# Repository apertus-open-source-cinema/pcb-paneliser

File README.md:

# pcb-paneliser
Creating panels from individual PCBs in an as automated way as possible.

## Setup
These scripts were built for python3.

  * Execute ```pip3 install -r requirements.txt``` to install required modules
  * Run ```python3 stage1_generate_mixed_beta_panel.py``` to generate mixed PCB panel
  * Run ```python3 stage2_generate_multi_mixed_beta_panel.py``` to generate a big panel consisting of multiple mixed PCB panels
  * Run ```python3 stage3_generate_stage1_stencils.py``` to generate stencils for mixed PCB panel

## Extracting impedance relevant layers

  * Update the filenames to extract in ```extract_impedance_stage1.py``` and then execute ```python3 extract_impedance_stage1.py``` - this extracts all traces with a specific netclass from the *.brd files and creates a new output file called <boardname>_impedance.brd inside output_impedance_filtered/
  * Extract gerber layers throught Eagles oshpark-4layer.cam into output_impedance_filtered/gerber_export and use rotate_90_ccw.sh on them if required.
  * Update output_impedance_filtered/stage1_generate_mixed_beta_impedance_panel.py again withe the correct board names and run ```python3 stage1_generate_mixed_beta_impedance_panel.py```

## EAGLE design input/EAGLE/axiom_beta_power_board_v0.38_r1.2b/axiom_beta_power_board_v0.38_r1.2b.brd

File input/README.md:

# Export from EAGLE to Gerber

This guide should cover the process to go from eagle _*.brd_ file to the catalog of Gerber input files for stage 1.

## Steps:
* Open _*.brd_ and _*.sch_ files in Eagle
* Choose assembly variant in dropdown menu then resave both _*.brd_ and _*.sch_ files
  * Select base (**empty** variant) for panels and **Tele** for stencil and BOM
* in Eagle go to **File -> CAM Processor**, then in the newly opened window **File -> Open -> Job**
* Choose the **oshpark-4layer.cam** file from this directory
* Click **Process Job** - the files will be written to the same directory where the _*.brd_ file resides
  * Confirm the warning about large data with **Yes to all**

# using the rotate script
copy the **rotate_90_ccw.sh** script into a subfolder containing gerber files like the **base_variant** folder.
Run **rotate_90_ccw.sh** with the name of the board and subfolder as argument.
It will rename the source to ..._original, but you should grab the data from the new folder and paste it over the original one, delete new folder and remove _original. Bit cumbersome currently but works for now.

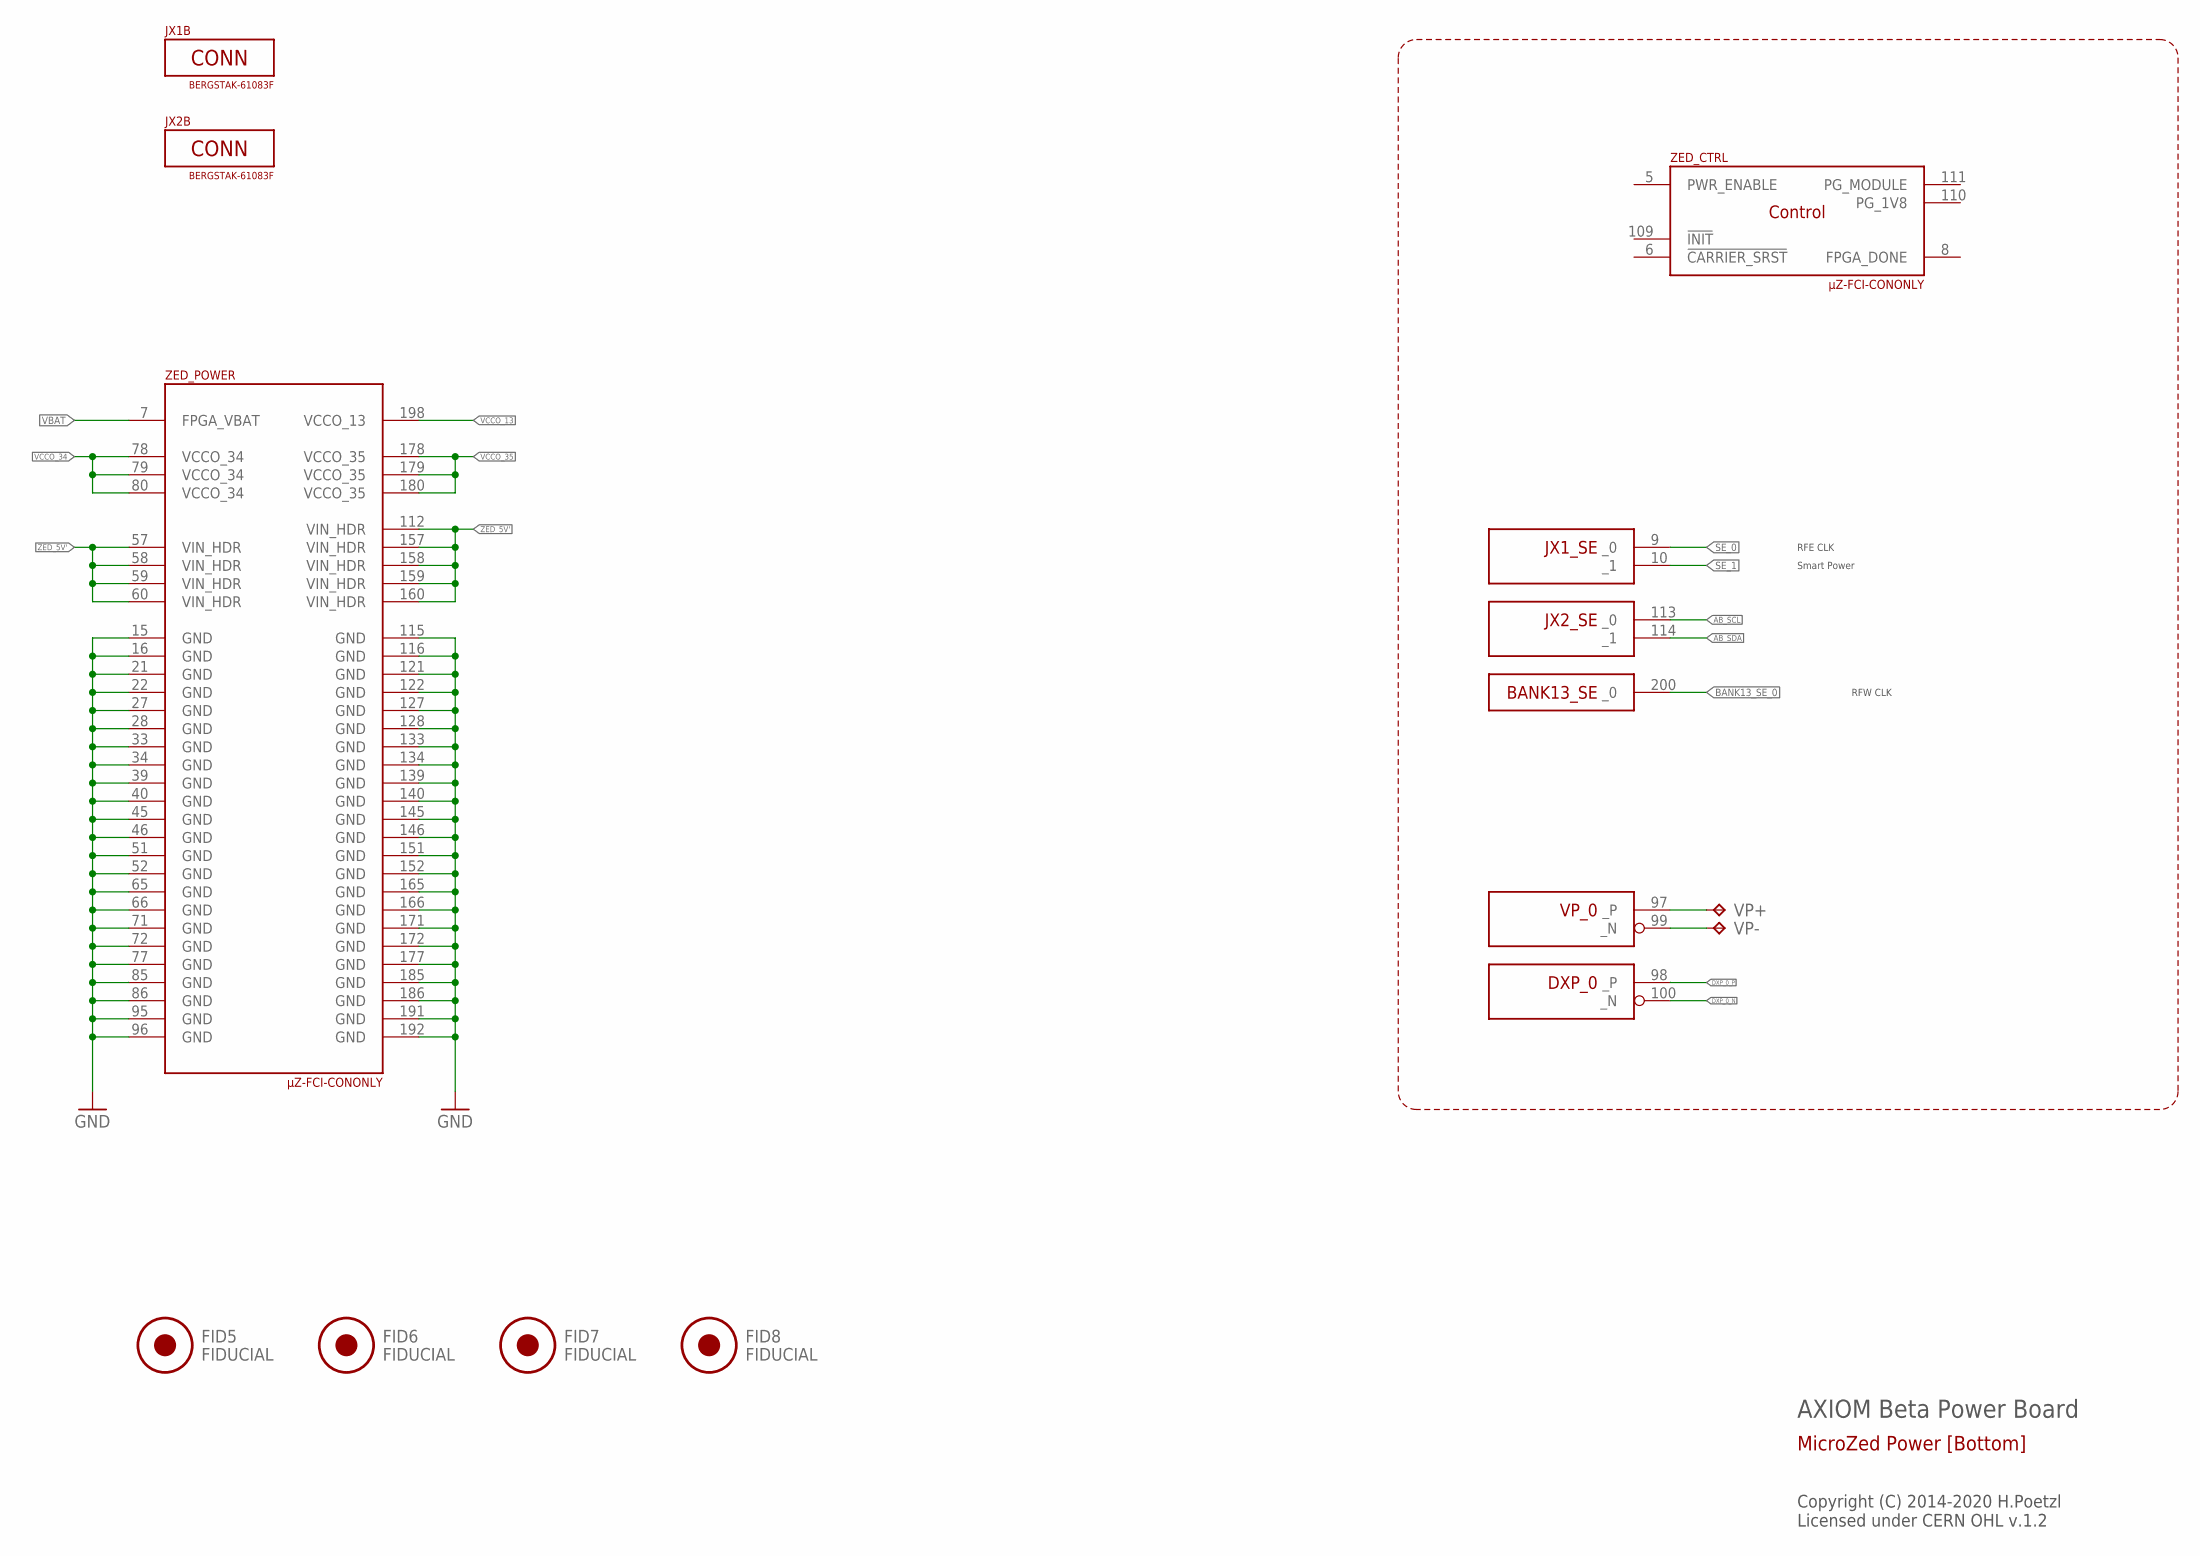
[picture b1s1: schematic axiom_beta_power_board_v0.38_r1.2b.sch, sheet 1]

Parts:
FID5, FID6, FID7, FID8: FIDUCIAL; FID_ARROW
JX1B, JX2B: BERGSTAK-61083F; 61083-FAKE
VP+: TPTP16SQ; TP16SQ
VP-: TPTP16SQ; TP16SQ
ZED: µZ-FCI-CONONLY; µZ-CONONLY

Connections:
AB_SCL: ZED.113 (_0); also elsewhere on the board
AB_SDA: ZED.114 (_1); also elsewhere on the board
BANK13_SE_0: ZED.200 (_0); also elsewhere on the board
DXP_0_N: ZED.100 (_N)
DXP_0_P: ZED.98 (_P)
GND: ZED.15 (GND), ZED.16 (GND), ZED.21 (GND), ZED.22 (GND), ZED.27 (GND), ZED.28 (GND), ZED.33 (GND), ZED.34 (GND), ZED.39 (GND), ZED.40 (GND), ZED.45 (GND), ZED.46 (GND), ZED.51 (GND), ZED.52 (GND), ZED.65 (GND), ZED.66 (GND), ZED.71 (GND), ZED.72 (GND), ZED.77 (GND), ZED.85 (GND), ZED.86 (GND), ZED.95 (GND), ZED.96 (GND), ZED.115 (GND), ZED.116 (GND), ZED.121 (GND), ZED.122 (GND), ZED.127 (GND), ZED.128 (GND), ZED.133 (GND), ZED.134 (GND), ZED.139 (GND), ZED.140 (GND), ZED.145 (GND), ZED.146 (GND), ZED.151 (GND), ZED.152 (GND), ZED.165 (GND), ZED.166 (GND), ZED.171 (GND), ZED.172 (GND), ZED.177 (GND), ZED.185 (GND), ZED.186 (GND), ZED.191 (GND), ZED.192 (GND); also elsewhere on the board
SE_0: ZED.9 (_0); also elsewhere on the board
SE_1: ZED.10 (_1); also elsewhere on the board
VBAT: ZED.7 (FPGA_VBAT)
VCCO_13: ZED.198 (VCCO_13); also elsewhere on the board
VCCO_34: ZED.78 (VCCO_34), ZED.79 (VCCO_34), ZED.80 (VCCO_34); also elsewhere on the board
VCCO_35: ZED.178 (VCCO_35), ZED.179 (VCCO_35), ZED.180 (VCCO_35); also elsewhere on the board
VP_0_N: VP-.TP, ZED.99 (_N)
VP_0_P: VP+.TP, ZED.97 (_P)
ZED_5V': ZED.57 (VIN_HDR), ZED.58 (VIN_HDR), ZED.59 (VIN_HDR), ZED.60 (VIN_HDR), ZED.112 (VIN_HDR), ZED.157 (VIN_HDR), ZED.158 (VIN_HDR), ZED.159 (VIN_HDR), ZED.160 (VIN_HDR); also elsewhere on the board

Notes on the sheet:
AXIOM Beta Power Board
Copyright (C) 2014-2020 H.Poetzl Licensed under CERN OHL v.1.2
MicroZed Power [Bottom]
Smart Power
RFE CLK
RFW CLK

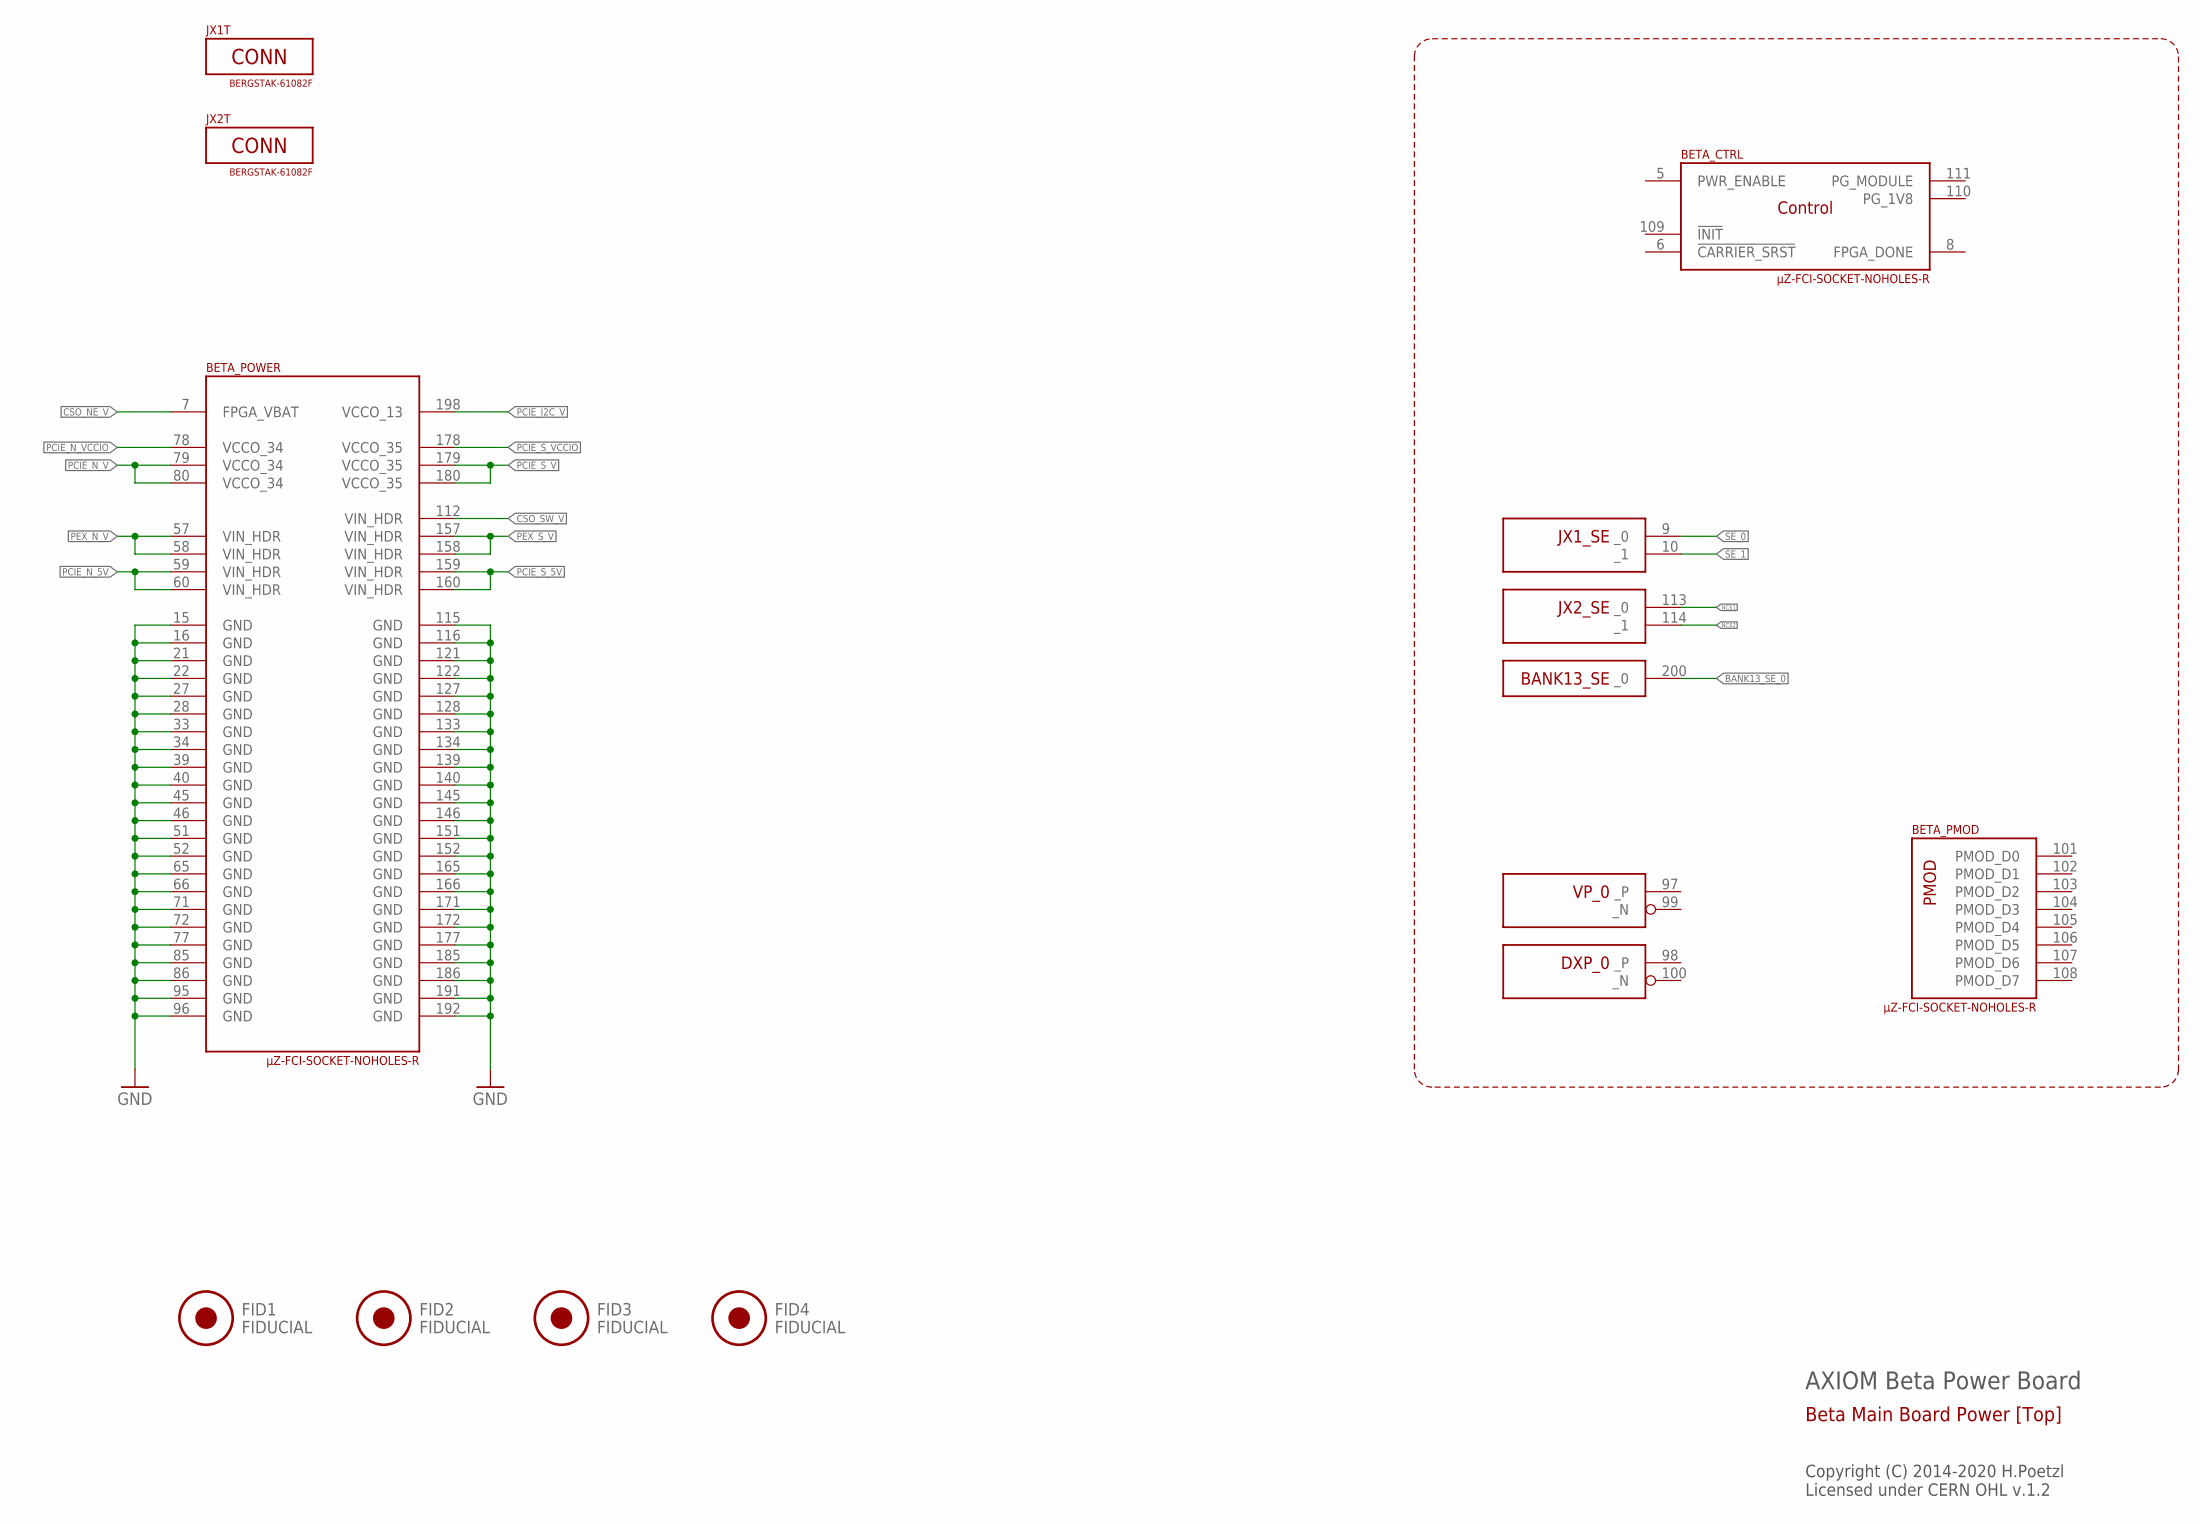
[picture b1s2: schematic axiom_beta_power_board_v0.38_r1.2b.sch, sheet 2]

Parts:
BETA: µZ-FCI-SOCKET-NOHOLES-R; µZ-SOCKET-NOHOLES-R
FID1, FID2, FID3, FID4: FIDUCIAL; FID_ARROW
JX1T, JX2T: BERGSTAK-61082F; 61082-FAKE

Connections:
BANK13_SE_0: BETA.200 (_0); also elsewhere on the board
CSO_NE_V: BETA.7 (FPGA_VBAT); also elsewhere on the board
CSO_SW_V: BETA.112 (VIN_HDR); also elsewhere on the board
GND: BETA.15 (GND), BETA.16 (GND), BETA.21 (GND), BETA.22 (GND), BETA.27 (GND), BETA.28 (GND), BETA.33 (GND), BETA.34 (GND), BETA.39 (GND), BETA.40 (GND), BETA.45 (GND), BETA.46 (GND), BETA.51 (GND), BETA.52 (GND), BETA.65 (GND), BETA.66 (GND), BETA.71 (GND), BETA.72 (GND), BETA.77 (GND), BETA.85 (GND), BETA.86 (GND), BETA.95 (GND), BETA.96 (GND), BETA.115 (GND), BETA.116 (GND), BETA.121 (GND), BETA.122 (GND), BETA.127 (GND), BETA.128 (GND), BETA.133 (GND), BETA.134 (GND), BETA.139 (GND), BETA.140 (GND), BETA.145 (GND), BETA.146 (GND), BETA.151 (GND), BETA.152 (GND), BETA.165 (GND), BETA.166 (GND), BETA.171 (GND), BETA.172 (GND), BETA.177 (GND), BETA.185 (GND), BETA.186 (GND), BETA.191 (GND), BETA.192 (GND); also elsewhere on the board
NC$1: BETA.113 (_0)
NC$2: BETA.114 (_1)
PCIE_I2C_V: BETA.198 (VCCO_13)
PCIE_N_5V: BETA.59 (VIN_HDR), BETA.60 (VIN_HDR)
PCIE_N_V: BETA.79 (VCCO_34), BETA.80 (VCCO_34); also elsewhere on the board
PCIE_N_VCCIO: BETA.78 (VCCO_34)
PCIE_S_5V: BETA.159 (VIN_HDR), BETA.160 (VIN_HDR)
PCIE_S_V: BETA.179 (VCCO_35), BETA.180 (VCCO_35); also elsewhere on the board
PCIE_S_VCCIO: BETA.178 (VCCO_35)
PEX_N_V: BETA.57 (VIN_HDR), BETA.58 (VIN_HDR)
PEX_S_V: BETA.157 (VIN_HDR), BETA.158 (VIN_HDR)
SE_0: BETA.9 (_0); also elsewhere on the board
SE_1: BETA.10 (_1); also elsewhere on the board

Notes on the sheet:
AXIOM Beta Power Board
Copyright (C) 2014-2020 H.Poetzl Licensed under CERN OHL v.1.2
Beta Main Board Power [Top]

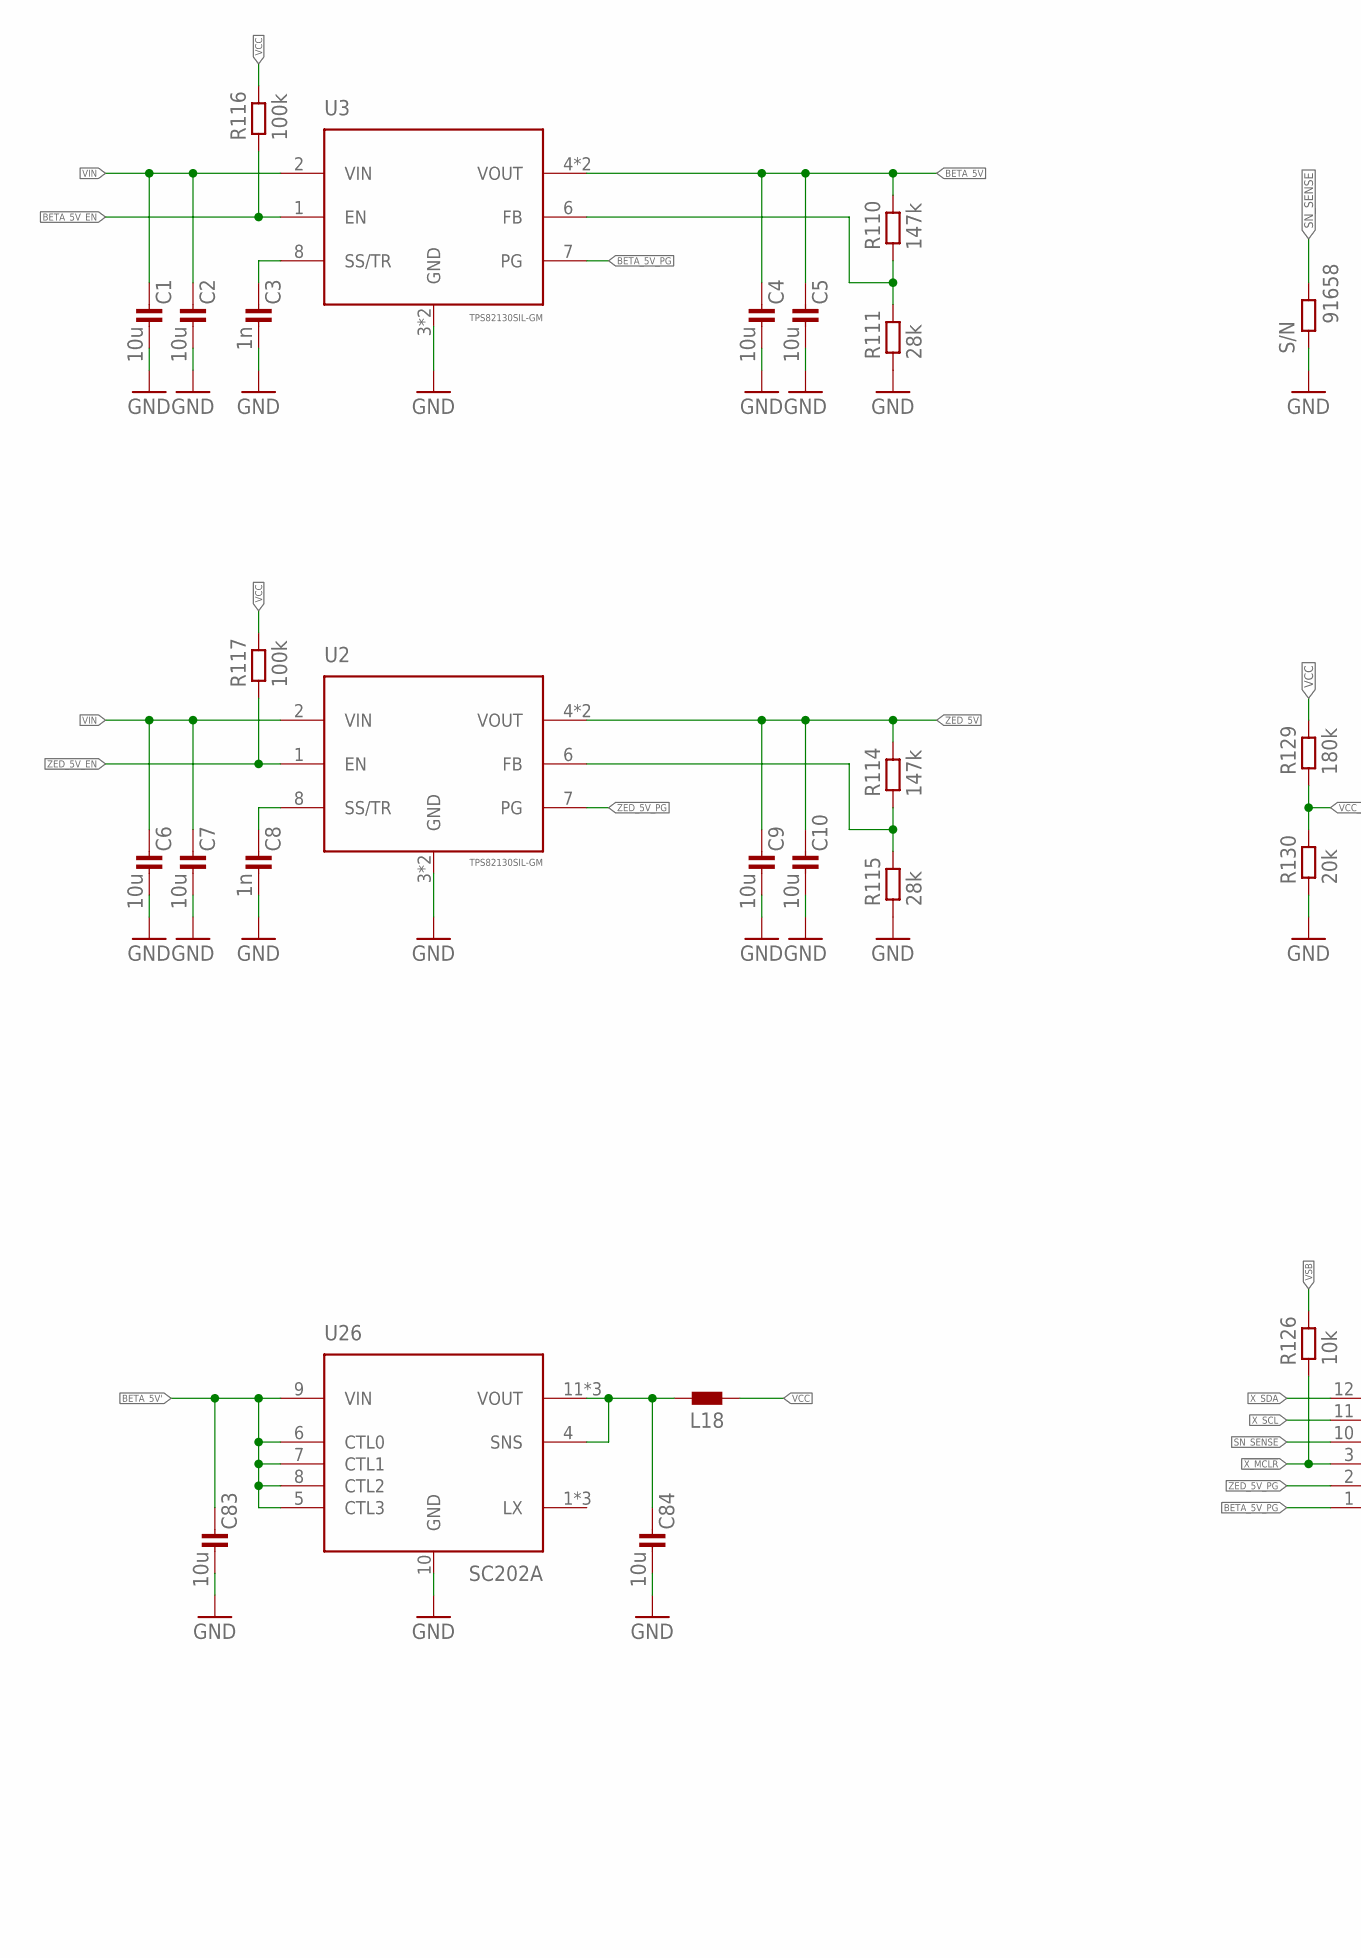
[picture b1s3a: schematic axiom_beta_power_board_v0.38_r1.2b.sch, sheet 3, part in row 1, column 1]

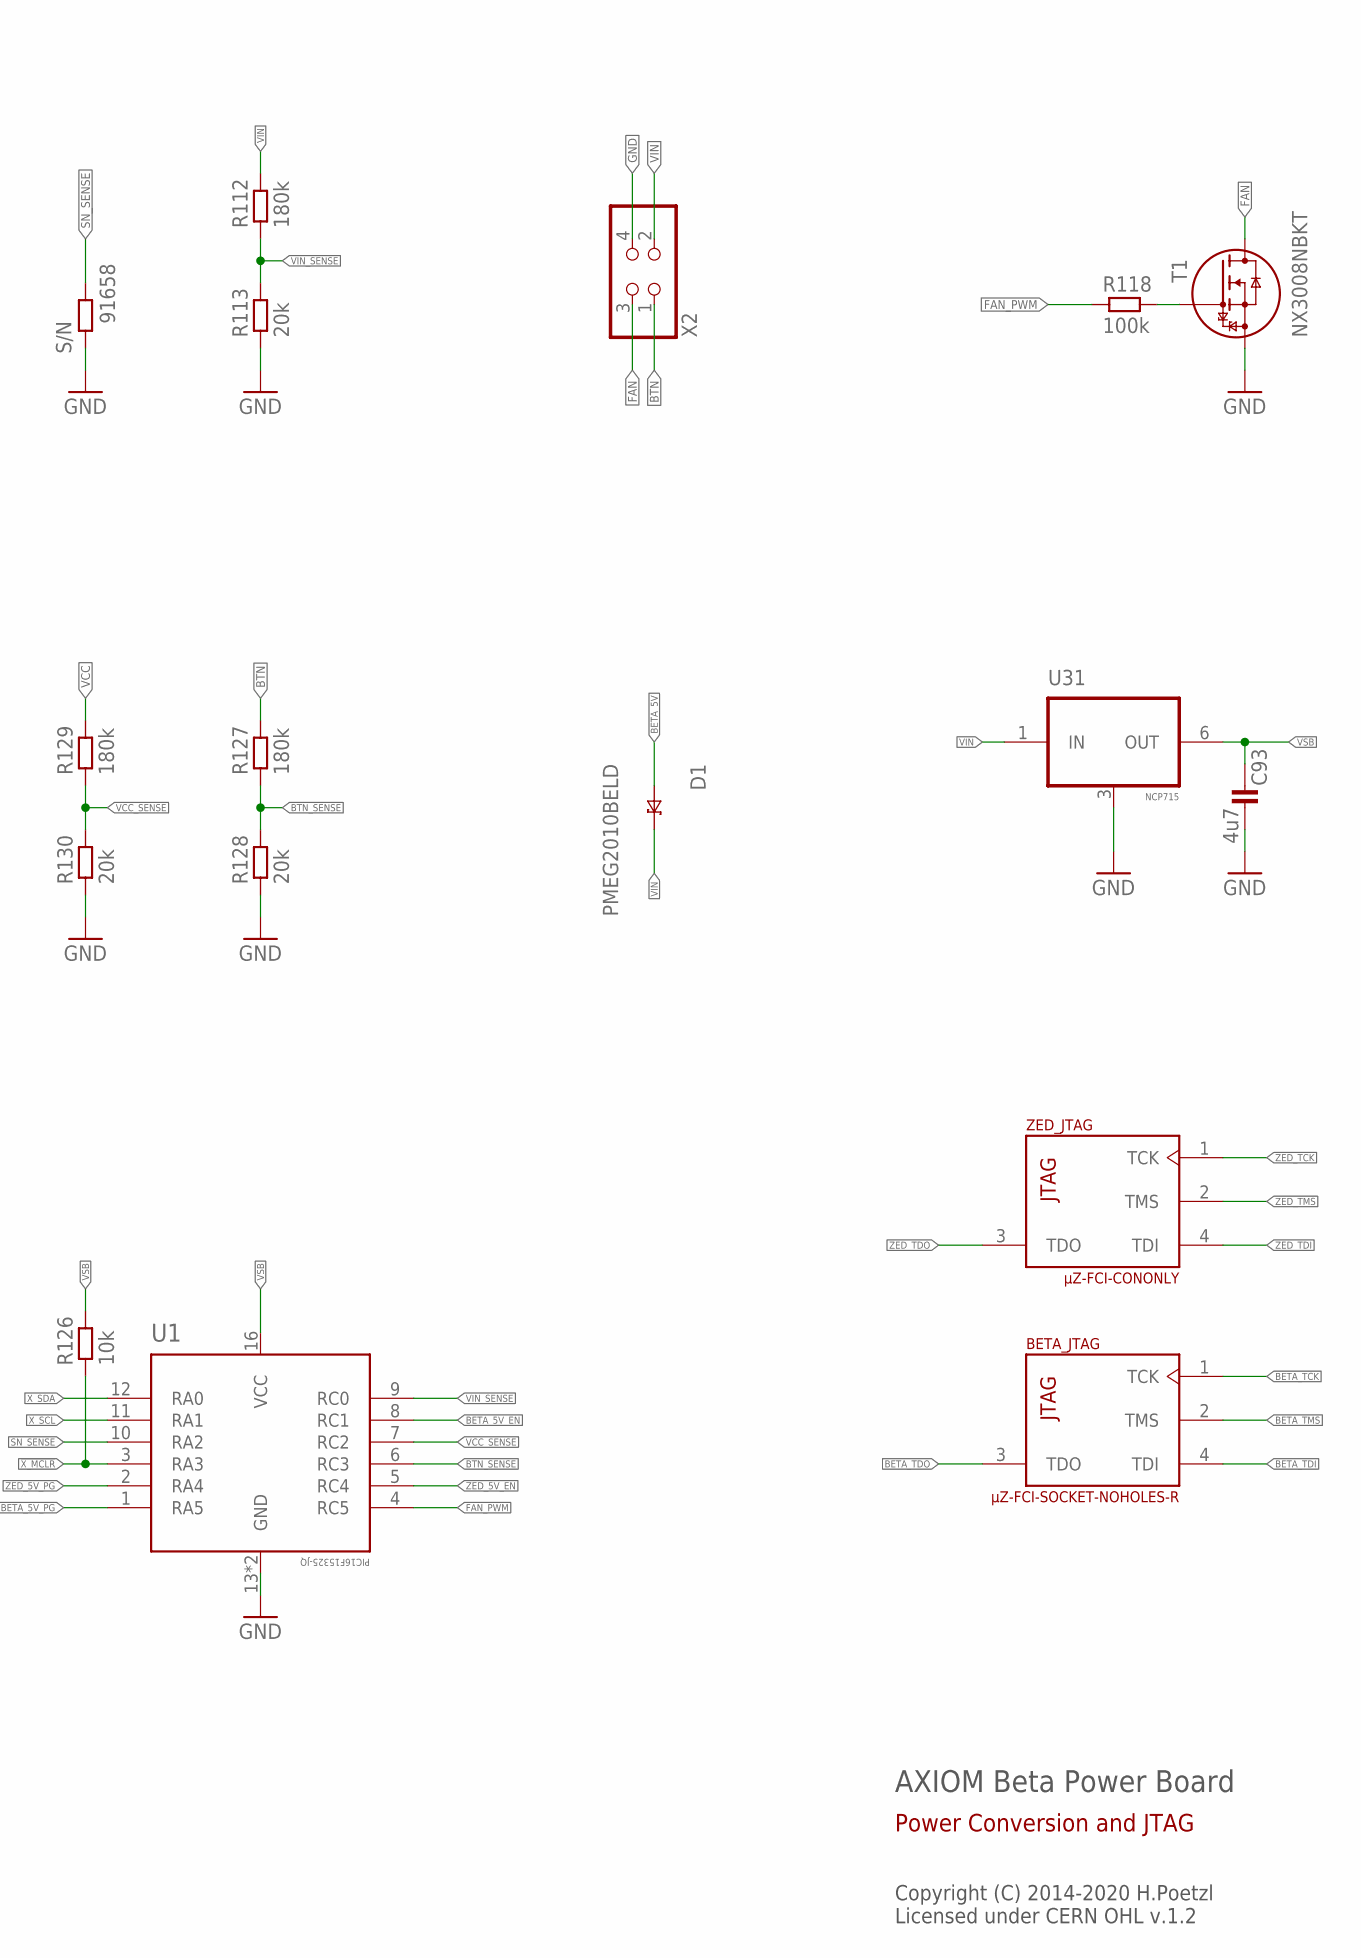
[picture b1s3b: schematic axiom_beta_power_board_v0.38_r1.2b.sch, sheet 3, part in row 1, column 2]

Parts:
BETA: µZ-FCI-SOCKET-NOHOLES-R; µZ-SOCKET-NOHOLES-R
C1, C5, C6, C10: 10u; 0603-B
C2, C4, C7, C9: 10u; 1206-C
C3, C8: 1n; 0402-C
C83, C84: 10u; 0603-C
C93: 4u7; 0402-B
D1: PMEG2010BELD; DFN1006D-2
L18: L0603-C; 0603-C
R110, R114: 147k; 0402-C
R111, R115: 28k; 0402-C
R112: 180k; 0402-B
R113: 20k; 0402-B
R116, R117: 100k; 0402-B
R118: 100k; 0402-C
R126: 10k; 0402-B
R127, R129: 180k; 0402-C
R128, R130: 20k; 0402-C
S/N: 91658; 3X2MM
T1: NX3008NBKT; SOT416
U1: PIC16F15325-JQ; UQFN65P400X400X100-17N
U2, U3: TPS82130SIL-GM; SIL0008D-GM
U26: SC202A; MLPQ-13
U31: NCP715; DFN150X150X50-6N
X2: PINHD-2X02_2.54-90°; 2X02/90
ZED: µZ-FCI-CONONLY; µZ-CONONLY

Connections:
!X_MCLR: R126.2, U1.3 (RA3); also elsewhere on the board
BETA_5V: C4.1, C5.1, D1.A, R110.1, U3.4 (VOUT), U3.5 (VOUT); also elsewhere on the board
BETA_5V': C83.1, U26.5 (CTL3), U26.6 (CTL0), U26.7 (CTL1), U26.8 (CTL2), U26.9 (VIN); also elsewhere on the board
BETA_5V_EN: R116.2, U1.8 (RC1), U3.1 (EN)
BETA_5V_PG: U1.1 (RA5), U3.7 (PG)
BETA_TCK: BETA.1 (TCK)
BETA_TDI: BETA.4 (TDI)
BETA_TDO: BETA.3 (TDO)
BETA_TMS: BETA.2 (TMS)
BTN: R127.1, X2.1
BTN_SENSE: R127.2, R128.1, U1.6 (RC3)
FAN: T1.3 (D), X2.3
FAN_PWM: R118.2, U1.4 (RC5)
GND: C1.2, C2.2, C3.2, C4.2, C5.2, C6.2, C7.2, C8.2, C9.2, C10.2, C83.2, C84.2, C93.2, R111.2, R113.2, R115.2, R128.2, R130.2, S/N.1, T1.2 (S), U1.13 (GND), U1.EP (GND), U2.3 (GND), U2.EPAD (GND), U3.3 (GND), U3.EPAD (GND), U26.10 (GND), U31.3 (GND), X2.4; also elsewhere on the board
unnamed: C8.1, U2.8 (SS/TR)
unnamed: C3.1, U3.8 (SS/TR)
unnamed: R118.1, T1.1 (G)
unnamed: R110.2, R111.1, U3.6 (FB)
unnamed: R114.2, R115.1, U2.6 (FB)
REGOUT: C84.1, L18.1, U26.4 (SNS), U26.11 (VOUT), U26.12 (VOUT), U26.13 (VOUT)
SN_SENSE: S/N.2, U1.10 (RA2)
VCC: L18.2, R116.1, R117.1, R129.1; also elsewhere on the board
VCC_SENSE: R129.2, R130.1, U1.7 (RC2)
VIN: C1.1, C2.1, C6.1, C7.1, D1.C (K), R112.1, U2.2 (VIN), U3.2 (VIN), U31.1 (IN), X2.2
VIN_SENSE: R112.2, R113.1, U1.9 (RC0)
VSB: C93.1, R126.1, U1.16 (VCC), U31.6 (OUT); also elsewhere on the board
X_SCL: U1.11 (RA1); also elsewhere on the board
X_SDA: U1.12 (RA0); also elsewhere on the board
ZED_5V: C9.1, C10.1, R114.1, U2.4 (VOUT), U2.5 (VOUT); also elsewhere on the board
ZED_5V_EN: R117.2, U1.5 (RC4), U2.1 (EN)
ZED_5V_PG: U1.2 (RA4), U2.7 (PG)
ZED_TCK: ZED.1 (TCK)
ZED_TDI: ZED.4 (TDI)
ZED_TDO: ZED.3 (TDO)
ZED_TMS: ZED.2 (TMS)

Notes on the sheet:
AXIOM Beta Power Board
Copyright (C) 2014-2020 H.Poetzl Licensed under CERN OHL v.1.2
Power Conversion and JTAG

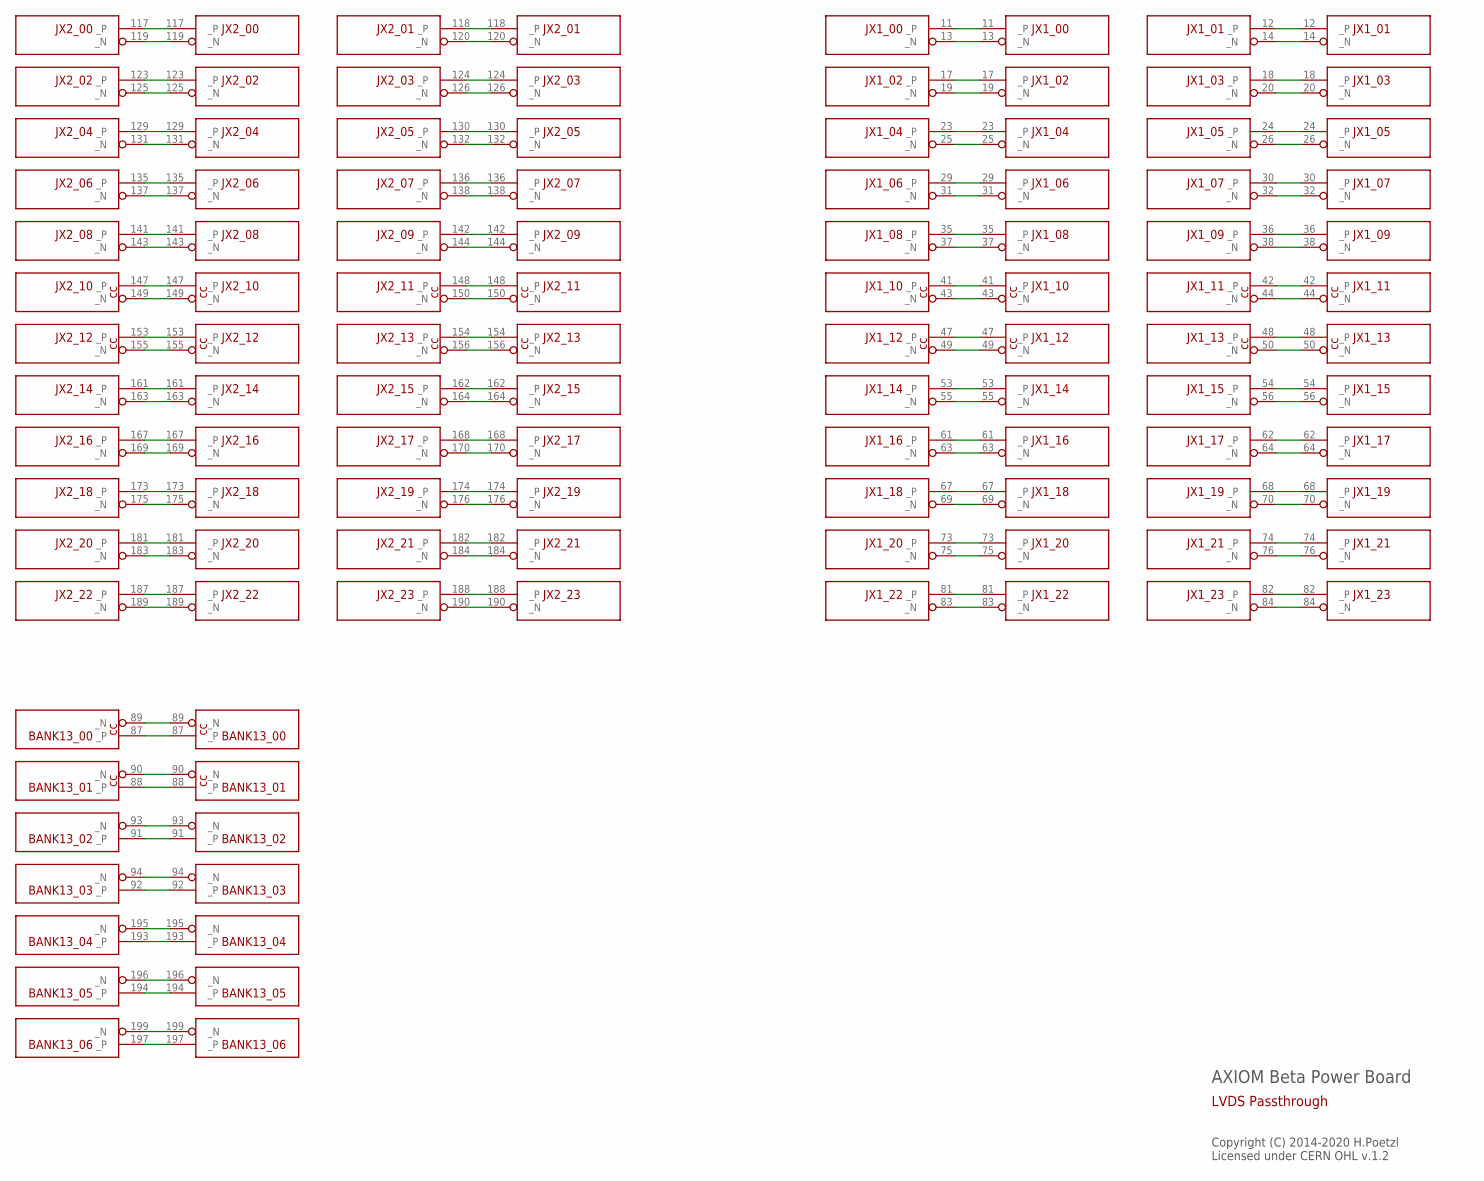
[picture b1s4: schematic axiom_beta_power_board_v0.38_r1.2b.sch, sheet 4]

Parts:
BETA: µZ-FCI-SOCKET-NOHOLES-R; µZ-SOCKET-NOHOLES-R
ZED: µZ-FCI-CONONLY; µZ-CONONLY

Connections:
BANK13_00_N: BETA.89 (_N), ZED.89 (_N)
BANK13_00_P: BETA.87 (_P), ZED.87 (_P)
BANK13_01_N: BETA.90 (_N), ZED.90 (_N)
BANK13_01_P: BETA.88 (_P), ZED.88 (_P)
BANK13_02_N: BETA.93 (_N), ZED.93 (_N)
BANK13_02_P: BETA.91 (_P), ZED.91 (_P)
BANK13_03_N: BETA.94 (_N), ZED.94 (_N)
BANK13_03_P: BETA.92 (_P), ZED.92 (_P)
BANK13_04_N: BETA.195 (_N), ZED.195 (_N)
BANK13_04_P: BETA.193 (_P), ZED.193 (_P)
BANK13_05_N: BETA.196 (_N), ZED.196 (_N)
BANK13_05_P: BETA.194 (_P), ZED.194 (_P)
BANK13_06_N: BETA.199 (_N), ZED.199 (_N)
BANK13_06_P: BETA.197 (_P), ZED.197 (_P)
JX1_00_N: BETA.13 (_N), ZED.13 (_N)
JX1_00_P: BETA.11 (_P), ZED.11 (_P)
JX1_01_N: BETA.14 (_N), ZED.14 (_N)
JX1_01_P: BETA.12 (_P), ZED.12 (_P)
JX1_02_N: BETA.19 (_N), ZED.19 (_N)
JX1_02_P: BETA.17 (_P), ZED.17 (_P)
JX1_03_N: BETA.20 (_N), ZED.20 (_N)
JX1_03_P: BETA.18 (_P), ZED.18 (_P)
JX1_04_N: BETA.25 (_N), ZED.25 (_N)
JX1_04_P: BETA.23 (_P), ZED.23 (_P)
JX1_05_N: BETA.26 (_N), ZED.26 (_N)
JX1_05_P: BETA.24 (_P), ZED.24 (_P)
JX1_06_N: BETA.31 (_N), ZED.31 (_N)
JX1_06_P: BETA.29 (_P), ZED.29 (_P)
JX1_07_N: BETA.32 (_N), ZED.32 (_N)
JX1_07_P: BETA.30 (_P), ZED.30 (_P)
JX1_08_N: BETA.37 (_N), ZED.37 (_N)
JX1_08_P: BETA.35 (_P), ZED.35 (_P)
JX1_09_N: BETA.38 (_N), ZED.38 (_N)
JX1_09_P: BETA.36 (_P), ZED.36 (_P)
JX1_10_N: BETA.43 (_N), ZED.43 (_N)
JX1_10_P: BETA.41 (_P), ZED.41 (_P)
JX1_11_N: BETA.44 (_N), ZED.44 (_N)
JX1_11_P: BETA.42 (_P), ZED.42 (_P)
JX1_12_N: BETA.49 (_N), ZED.49 (_N)
JX1_12_P: BETA.47 (_P), ZED.47 (_P)
JX1_13_N: BETA.50 (_N), ZED.50 (_N)
JX1_13_P: BETA.48 (_P), ZED.48 (_P)
JX1_14_N: BETA.55 (_N), ZED.55 (_N)
JX1_14_P: BETA.53 (_P), ZED.53 (_P)
JX1_15_N: BETA.56 (_N), ZED.56 (_N)
JX1_15_P: BETA.54 (_P), ZED.54 (_P)
JX1_16_N: BETA.63 (_N), ZED.63 (_N)
JX1_16_P: BETA.61 (_P), ZED.61 (_P)
JX1_17_N: BETA.64 (_N), ZED.64 (_N)
JX1_17_P: BETA.62 (_P), ZED.62 (_P)
JX1_18_N: BETA.69 (_N), ZED.69 (_N)
JX1_18_P: BETA.67 (_P), ZED.67 (_P)
JX1_19_N: BETA.70 (_N), ZED.70 (_N)
JX1_19_P: BETA.68 (_P), ZED.68 (_P)
JX1_20_N: BETA.75 (_N), ZED.75 (_N)
JX1_20_P: BETA.73 (_P), ZED.73 (_P)
JX1_21_N: BETA.76 (_N), ZED.76 (_N)
JX1_21_P: BETA.74 (_P), ZED.74 (_P)
JX1_22_N: BETA.83 (_N), ZED.83 (_N)
JX1_22_P: BETA.81 (_P), ZED.81 (_P)
JX1_23_N: BETA.84 (_N), ZED.84 (_N)
JX1_23_P: BETA.82 (_P), ZED.82 (_P)
JX2_00_N: BETA.119 (_N), ZED.119 (_N)
JX2_00_P: BETA.117 (_P), ZED.117 (_P)
JX2_01_N: BETA.120 (_N), ZED.120 (_N)
JX2_01_P: BETA.118 (_P), ZED.118 (_P)
JX2_02_N: BETA.125 (_N), ZED.125 (_N)
JX2_02_P: BETA.123 (_P), ZED.123 (_P)
JX2_03_N: BETA.126 (_N), ZED.126 (_N)
JX2_03_P: BETA.124 (_P), ZED.124 (_P)
JX2_04_N: BETA.131 (_N), ZED.131 (_N)
JX2_04_P: BETA.129 (_P), ZED.129 (_P)
JX2_05_N: BETA.132 (_N), ZED.132 (_N)
JX2_05_P: BETA.130 (_P), ZED.130 (_P)
JX2_06_N: BETA.137 (_N), ZED.137 (_N)
JX2_06_P: BETA.135 (_P), ZED.135 (_P)
JX2_07_N: BETA.138 (_N), ZED.138 (_N)
JX2_07_P: BETA.136 (_P), ZED.136 (_P)
JX2_08_N: BETA.143 (_N), ZED.143 (_N)
JX2_08_P: BETA.141 (_P), ZED.141 (_P)
JX2_09_N: BETA.144 (_N), ZED.144 (_N)
JX2_09_P: BETA.142 (_P), ZED.142 (_P)
JX2_10_N: BETA.149 (_N), ZED.149 (_N)
JX2_10_P: BETA.147 (_P), ZED.147 (_P)
JX2_11_N: BETA.150 (_N), ZED.150 (_N)
JX2_11_P: BETA.148 (_P), ZED.148 (_P)
JX2_12_N: BETA.155 (_N), ZED.155 (_N)
JX2_12_P: BETA.153 (_P), ZED.153 (_P)
JX2_13_N: BETA.156 (_N), ZED.156 (_N)
JX2_13_P: BETA.154 (_P), ZED.154 (_P)
JX2_14_N: BETA.163 (_N), ZED.163 (_N)
JX2_14_P: BETA.161 (_P), ZED.161 (_P)
JX2_15_N: BETA.164 (_N), ZED.164 (_N)
JX2_15_P: BETA.162 (_P), ZED.162 (_P)
JX2_16_N: BETA.169 (_N), ZED.169 (_N)
JX2_16_P: BETA.167 (_P), ZED.167 (_P)
JX2_17_N: BETA.170 (_N), ZED.170 (_N)
JX2_17_P: BETA.168 (_P), ZED.168 (_P)
JX2_18_N: BETA.175 (_N), ZED.175 (_N)
JX2_18_P: BETA.173 (_P), ZED.173 (_P)
JX2_19_N: BETA.176 (_N), ZED.176 (_N)
JX2_19_P: BETA.174 (_P), ZED.174 (_P)
JX2_20_N: BETA.183 (_N), ZED.183 (_N)
JX2_20_P: BETA.181 (_P), ZED.181 (_P)
JX2_21_N: BETA.184 (_N), ZED.184 (_N)
JX2_21_P: BETA.182 (_P), ZED.182 (_P)
JX2_22_N: BETA.189 (_N), ZED.189 (_N)
JX2_22_P: BETA.187 (_P), ZED.187 (_P)
JX2_23_N: BETA.190 (_N), ZED.190 (_N)
JX2_23_P: BETA.188 (_P), ZED.188 (_P)

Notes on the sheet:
AXIOM Beta Power Board
Copyright (C) 2014-2020 H.Poetzl Licensed under CERN OHL v.1.2
LVDS Passthrough

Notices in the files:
input/EAGLE/axiom_beta_power_board_v0.38_r1.2b/axiom_beta_power_board_v0.38_r1.2b.brd:
Copyright (C) 2015-2020 H.Pötzl
input/tele_variant/axiom_beta_interface_dummy_v0.13_r1.3/axiom_beta_interface_dummy_v0.13_r1.3.brd:
Copyright (C) 2015 Herbert Pötzl
